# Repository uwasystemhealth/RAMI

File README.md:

# Remote Asset Management Indicator (RAMI)

This is a companion repository to the paper
_Sensing system for low cost condition monitoring of remote assets_
by Aiden J Ziegelaar, Ben C Travaglione & Melinda R Hodkiewicz,
published in
[4th IFAC Workshop on Advanced Maintenance Engineering, Services and Technologies](https://www.amest2020.eng.cam.ac.uk/).

This repository contains all the information necessary to replicate the results presented in the paper.

The majority of the notes are contained within the [Jupyter](https://jupyter.org/) notebook [RAMI.ipynb](RAMI.ipynb).

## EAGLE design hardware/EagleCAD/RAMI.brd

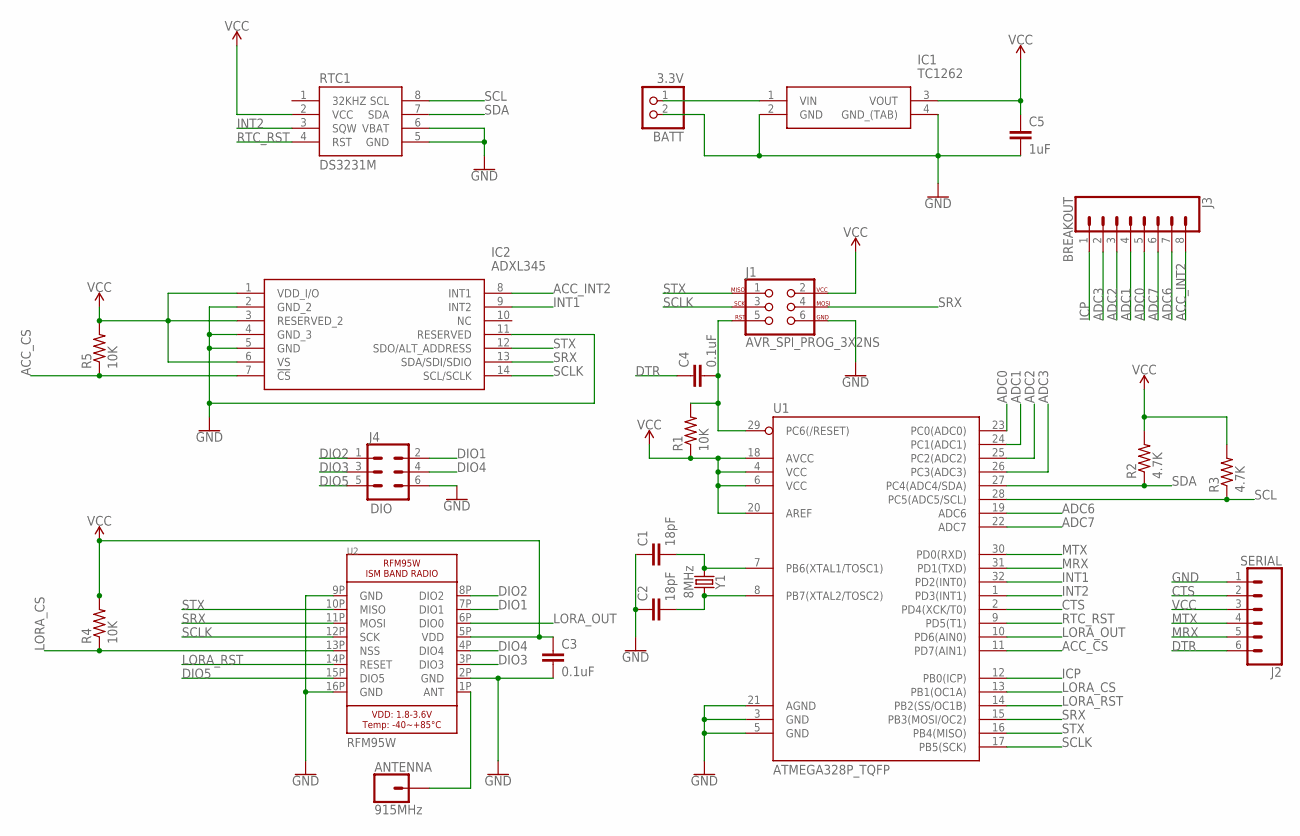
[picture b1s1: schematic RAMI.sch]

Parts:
ANTENNA: 915MHz; 1X01
BATT: 3.3V; JST-PH-2-THM
C1, C2: 18pF; 0603
C3, C4: 0.1uF; 0603
C5: 1uF; C050-024X044
IC1: TC1262; SOT230P700X180-4N
IC2: ADXL345; LGA14R80P3X6_300X500X100
J1: AVR_SPI_PROG_3X2NS; 2X3-NS
J2: SERIAL; 1X06_LOCK
J3: BREAKOUT; 1X08
J4: DIO; 2X3-NS
R1, R4, R5: 10K; R0603
R2, R3: 4.7K; R0603
RTC1: DS3231M; SO08
U1: ATMEGA328P_TQFP; TQFP32-08
U2: RFM95W; RFM95W_SMT
Y1: 8MHz; HC49US

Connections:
ACC_CS: IC2.7 (!CS), R5.1, U1.11 (PD7(AIN1))
ACC_INT2: IC2.8 (INT1), J3.8
ADC0: J3.5, U1.23 (PC0(ADC0))
ADC1: J3.4, U1.24 (PC1(ADC1))
ADC2: J3.3, U1.25 (PC2(ADC2))
ADC3: J3.2, U1.26 (PC3(ADC3))
ADC6: J3.7, U1.19 (ADC6)
ADC7: J3.6, U1.22 (ADC7)
ANT: ANTENNA.1, U2.1P (ANT)
CTS: J2.2, U1.2 (PD4(XCK/T0))
DIO1: J4.2, U2.7P (DIO1)
DIO2: J4.1, U2.8P (DIO2)
DIO3: J4.3, U2.3P (DIO3)
DIO4: J4.4, U2.4P (DIO4)
DIO5: J4.5, U2.15P (DIO5)
DTR: C4.1, J2.6
GND: BATT.2 (1), C1.1, C2.1, C3.2, C5.2, IC1.2 (GND), IC1.4 (GND_(TAB)), IC2.2 (GND_2), IC2.4 (GND_3), IC2.5 (GND), IC2.11 (RESERVED), J1.6, J2.1, J4.6, RTC1.5 (GND), RTC1.6 (VBAT), U1.3 (GND), U1.5 (GND), U1.21 (AGND), U2.2P (GND), U2.9P (GND), U2.16P (GND)
ICP: J3.1, U1.12 (PB0(ICP))
INT1: IC2.9 (INT2), U1.32 (PD2(INT0))
INT2: RTC1.3 (SQW), U1.1 (PD3(INT1))
LORA_CS: R4.1, U1.13 (PB1(OC1A)), U2.13P (NSS)
LORA_OUT: U1.10 (PD6(AIN0)), U2.6P (DIO0)
LORA_RST: U1.14 (PB2(SS/OC1B)), U2.14P (RESET)
MRX: J2.5, U1.31 (PD1(TXD))
MTX: J2.4, U1.30 (PD0(RXD))
unnamed: C1.2, U1.7 (PB6(XTAL1/TOSC1)), Y1.1
unnamed: C2.2, U1.8 (PB7(XTAL2/TOSC2)), Y1.2
unnamed: BATT.1 (2), IC1.1 (VIN)
RST: C4.2, J1.5, R1.2, U1.29 (PC6(/RESET))
RTC_RST: RTC1.4 (RST), U1.9 (PD5(T1))
SCL: R3.1, RTC1.8 (SCL), U1.28 (PC5(ADC5/SCL))
SCLK: IC2.14 (SCL/SCLK), J1.3, U1.17 (PB5(SCK)), U2.12P (SCK)
SDA: R2.1, RTC1.7 (SDA), U1.27 (PC4(ADC4/SDA))
SRX: IC2.13 (SDA/SDI/SDIO), J1.4, U1.15 (PB3(MOSI/OC2)), U2.11P (MOSI)
STX: IC2.12 (SDO/ALT_ADDRESS), J1.1, U1.16 (PB4(MISO)), U2.10P (MISO)
VCC: C3.1, C5.1, IC1.3 (VOUT), IC2.1 (VDD_I/O), IC2.3 (RESERVED_2), IC2.6 (VS), J1.2, J2.3, R1.1, R2.2, R3.2, R4.2, R5.2, RTC1.2 (VCC), U1.4 (VCC), U1.6 (VCC), U1.18 (AVCC), U1.20 (AREF), U2.5P (VDD)

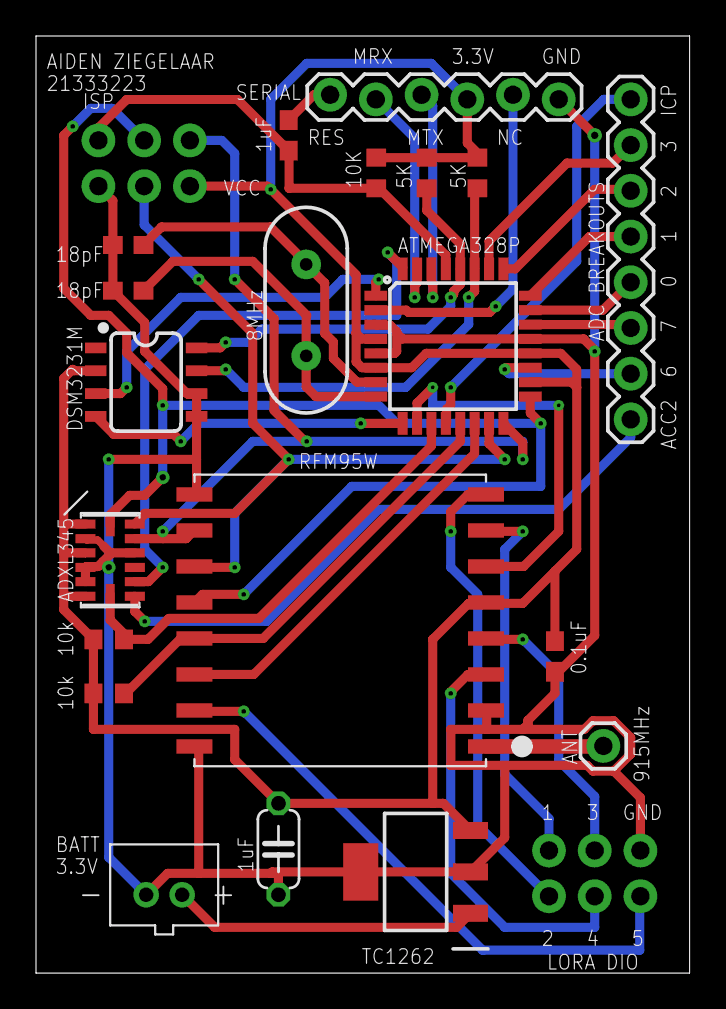
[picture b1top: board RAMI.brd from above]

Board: 2 copper layers, 36.3 x 52.1 mm, 22 parts (0 on the bottom side), 36 nets.

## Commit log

2020-05-06 Initial commit.
2020-05-08 Expanded hardware description in RAMI notebook
2020-05-08 Figures should now work in github notebook viewer

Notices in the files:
parts and their libraries:
SparkFun-Connectors: Licensing: Creative Commons ShareAlike 4.0 International - https://creativecommons.org/licenses/by-sa/4.0
